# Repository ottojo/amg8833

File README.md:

# AMG8833 Wemos D1 mini

This is a shield for the "Wemos D1 mini" ESP8266 board.
It contains a AMG8833 thermal sensor array, three WS2812 (Neopixel) LEDs and a 5V-logic-level output for interfacing additional RGB LEDs.

Top Side|Bottom Side
:-------------------------:|:-------------------------:
|
|

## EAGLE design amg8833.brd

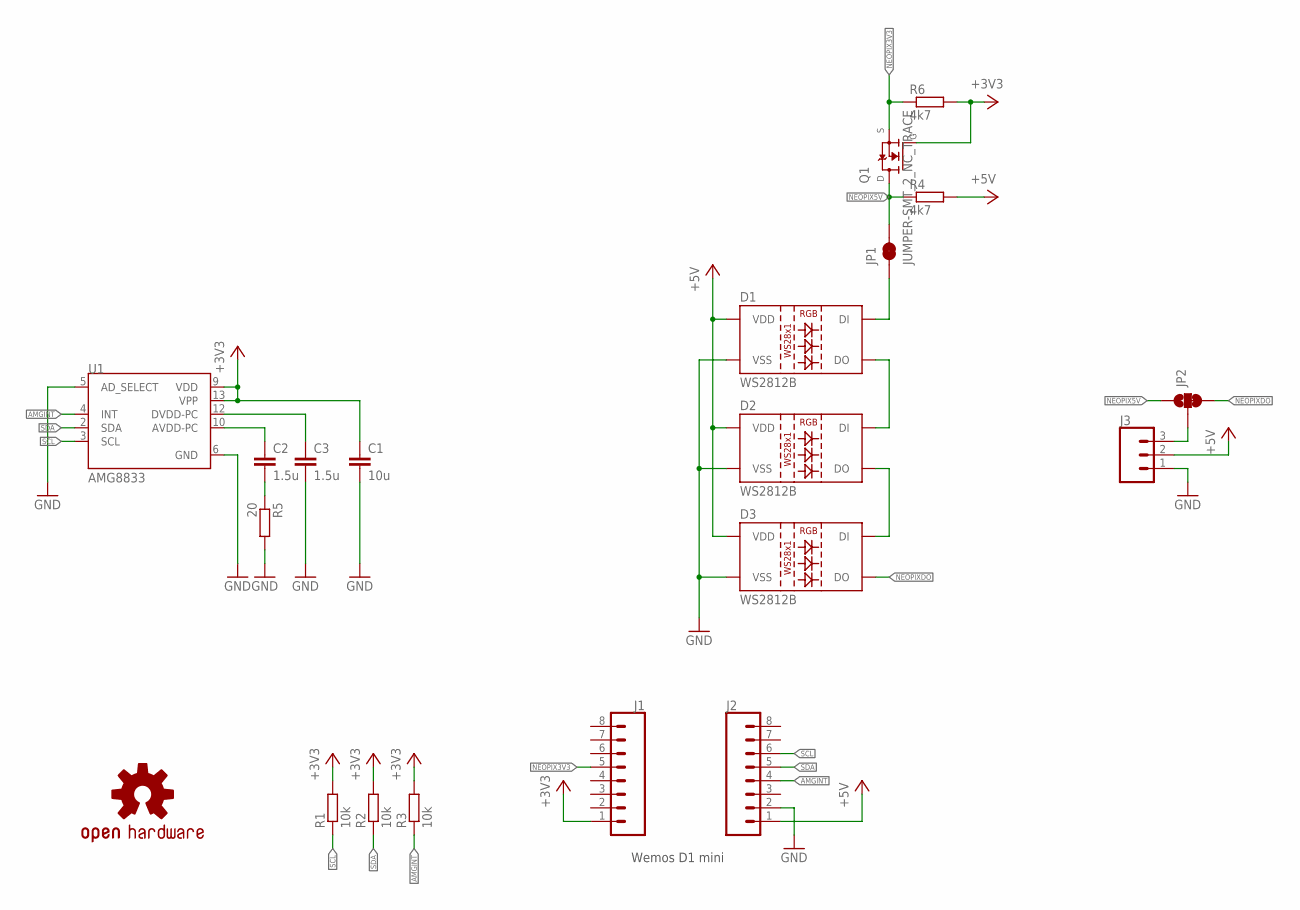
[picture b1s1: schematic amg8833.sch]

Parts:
C1: 10u; C0603
C2, C3: 1.5u; C0603
D1, D2, D3: WS2812B
J1, J2: CONN_08; 1X08_LOCK_NO_SILK
J3: CONN_03SCREWTERMINAL-3.5MM-3-NS; SCREWTERMINAL-3.5MM-3-NS
JP1: JUMPER-SMT_2_NC_TRACE; SMT-JUMPER_2_NC_TRACE_SILK
JP2: JUMPER-SMT_3_1-NC_TRACE; SMT-JUMPER_3_1-NC_TRACE_SILK
LOGO1: OSHW-LOGO; OSHW-LOGO-M
Q1: BSN20,215; BSN20_215
R1, R2, R3: 10k; R0603
R4, R6: 4k7; R0603
R5: 20; R0603
U1: AMG8833; XDCR_AMG8833

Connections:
+3V3: C1.1, J1.1, Q1.1 (G), R1.2, R2.2, R3.2, R6.2, U1.9 (VDD), U1.13 (VPP)
+5V: D1.1 (VDD), D2.1 (VDD), D3.1 (VDD), J2.1, J3.2, R4.2
AMGINT: J2.4, R3.1, U1.4 (INT)
GND: C1.2, C3.2, D1.3 (VSS), D2.3 (VSS), D3.3 (VSS), J2.2, J3.1, R5.2, U1.5 (AD_SELECT), U1.6 (GND)
MEOPIXOUT: J3.3, JP2.2
unnamed: C3.1, U1.12 (DVDD-PC)
unnamed: C2.1, U1.10 (AVDD-PC)
unnamed: D1.2 (DO), D2.4 (DI)
unnamed: D2.2 (DO), D3.4 (DI)
unnamed: D1.4 (DI), JP1.1
unnamed: C2.2, R5.1
NEOPIX3V3: J1.5, Q1.2 (S), R6.1
NEOPIX5V: JP1.2, JP2.1, Q1.3 (D), R4.1
NEOPIXDO: D3.2 (DO), JP2.3
SCL: J2.6, R1.1, U1.3 (SCL)
SDA: J2.5, R2.1, U1.2 (SDA)

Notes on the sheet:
Wemos D1 mini

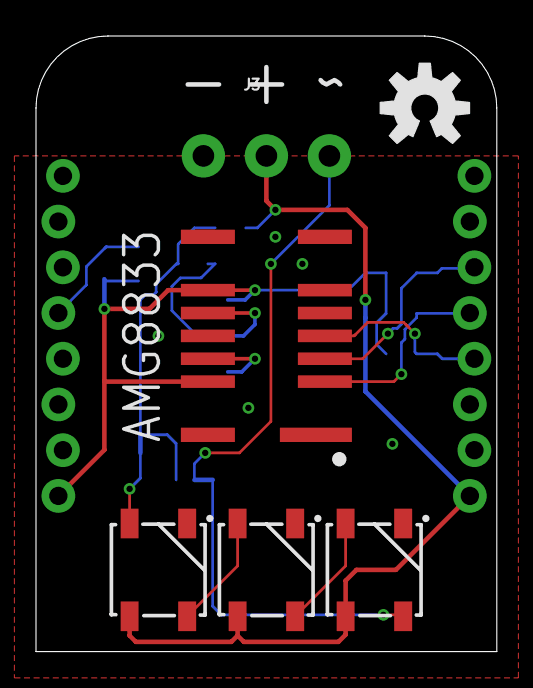
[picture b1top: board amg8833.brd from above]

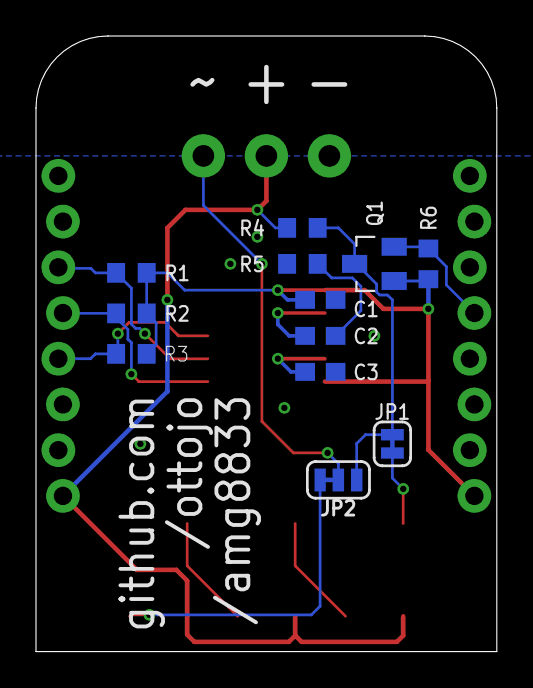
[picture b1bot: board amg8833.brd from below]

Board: 2 copper layers, 25.6 x 34.2 mm, 20 parts (12 on the bottom side), 16 nets.

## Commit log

2018-06-24 Added LICENSE
2018-06-25 fixes #1, #2
2018-06-25 silkscreen/naming fixes
2018-06-25 fixed gnd path
2018-06-25 updated images
2018-06-25 fixed outline
2018-06-30 3d stuff
